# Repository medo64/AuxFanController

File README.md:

# AuxFanController

Allows for PWM control of 4 fans based on the on-board temperature reaading.

Features:
* supports up to 3 fans
* temperature controlled speed
* short startup burst to avoid stall

## PWM Ranges

| Temperature |  PWM                      |
|:-----------:|---------------------------|
|   < 40 °C   |  10%                      |
|  40-80 °C   |  10-75% (linear increase) |
|    >80 °C   | 100%                      |

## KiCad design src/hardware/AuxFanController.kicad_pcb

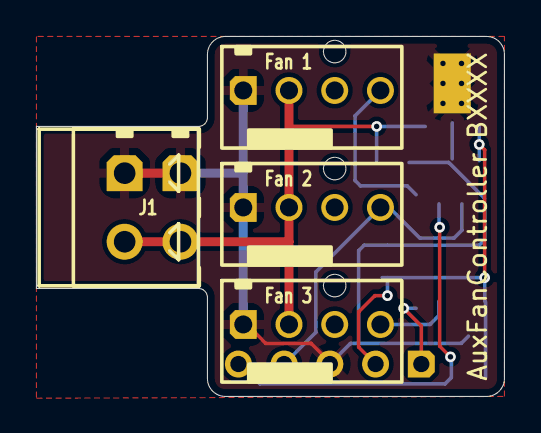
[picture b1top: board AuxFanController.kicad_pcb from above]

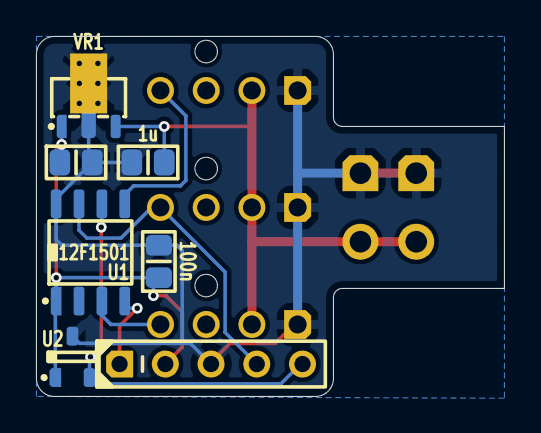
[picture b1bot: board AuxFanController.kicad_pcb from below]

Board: 2 copper layers, 26.0 x 20.0 mm, 12 parts (7 on the bottom side), 8 nets.

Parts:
C1, C2: 100n; C (0805)
C3: 1u; C (0805)
ICSP: Microchip PIC; ICSP PIC Pogo SS (5w)
J1: MC 1,5/2; J Phoenix MC (2w)
J1': MCV 1,5/2; J Phoenix MCV (2w)
J2: Fan 1; J Molex 047053 [Fan] (4w)
J3: Fan 2; J Molex 047053 [Fan] (4w)
J4: Fan 3; J Molex 047053 [Fan] (4w)
U1: 12F1501; U Micro [PIC12F1501] (SOIC-8)
U2: MCP9701A; U Temperature Analog [MCP9701] (SOT23-3)
VR1: AS78L05RTR; VR Linear 5V 100mA [AS78L05RTR-E1] (SOT89-3')

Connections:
+5V: C1.1, C2.1, ICSP.2, U1.1, U2.1, VR1.1
+12V: C3.1, J1.2, J1'.2, J2.2, J3.2, J4.2, VR1.3
ADC_TEMPERATURE: ICSP.5, U1.6, U2.2
GND: C1.2, C2.2, C3.2, ICSP.3, J1.1, J1'.1, J2.1, J3.1, J4.1, U1.8, U2.3, VR1.2
ICSP_VPP: ICSP.1, U1.4
OUT_PWM1: J2.4, U1.5
OUT_PWM2: ICSP.4, J3.4, U1.7
OUT_PWM3: J4.4, U1.3

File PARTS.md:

## AuxFanController Parts

|      |                           |
|------|---------------------------|
| Size | 26.0 x 20.0 mm ~ 0.9 sqin |


### Parts

|  # | Part name                                    | RefDes  | DigiKey PN                   |
|---:|----------------------------------------------|---------|------------------------------|
|  2 | C 100nF X7R 50V (0805)                       | C1-C2   | 478-5311-1-ND                |
|  1 | C 1uF X7R 25V (0805)                         | C3      | 1276-1066-1-ND               |
|  1 | J MC 1,5/ 2-G-3,81                           | J1†     | 277-1206-ND -or- 277-1221-ND |
|  3 | J Fan PWM (4w)                               | J2-J4   | WM4330-ND                    |
|  1 | U Micro [PIC12F1501] (SOIC-8)                | U1      | PIC12F1501-I/SN-ND           |
|  1 | U Temperature Analog [MCP9701A] (SOT23-3)    | U2      | MCP9701AT-E/TTCT-ND          |
|  1 | VR Linear 5V 100mA [AS78L05RTR-E1] (SOT89-3) | VR1     | AS78L05RTR-E1DICT-ND         |
|  1 | P Phoenix MC 1,5/ 2-ST-3,81 (2w)             | P1      | 277-1161-ND                  |

† Alternate PN is for vertical variant


### Pin Usage

|  # | Pin | ICSP | Function | Description        |
|---:|:---:|------|----------|--------------------|
|  1 | Vdd | Vdd  |          |                    |
|  2 | RA5 |      |          |                    |
|  3 | RA4 |      | PWM3     | Fan 3 Control      |
|  4 | RA3 | Vpp  |          |                    |
|  5 | RA2 |      | PWM1     | Fan 1 Control      |
|  6 | RA1 | Clk  | AN1      | Temperature sensor |
|  7 | RA0 | Dat  | PWM2     | Fan 2 Control      |
|  8 | Vss | Vss  |          |                    |

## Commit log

2025-07-19 Initial commit (move from AuxPower1U)
2025-07-19 Refactoring to make board smaller
2025-07-19 Added fan shroud
2025-07-19 Updated board refdes
2025-07-20 Updated part numbers
2025-08-31 Readded 4th channel
2025-08-31 Cleanup
2025-09-15 Fixed minimum spec. speed
2025-09-15 Adjusted fan curve
